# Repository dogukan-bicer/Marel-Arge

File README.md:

# Marel-Arge
marel arge çalışma dosyaları

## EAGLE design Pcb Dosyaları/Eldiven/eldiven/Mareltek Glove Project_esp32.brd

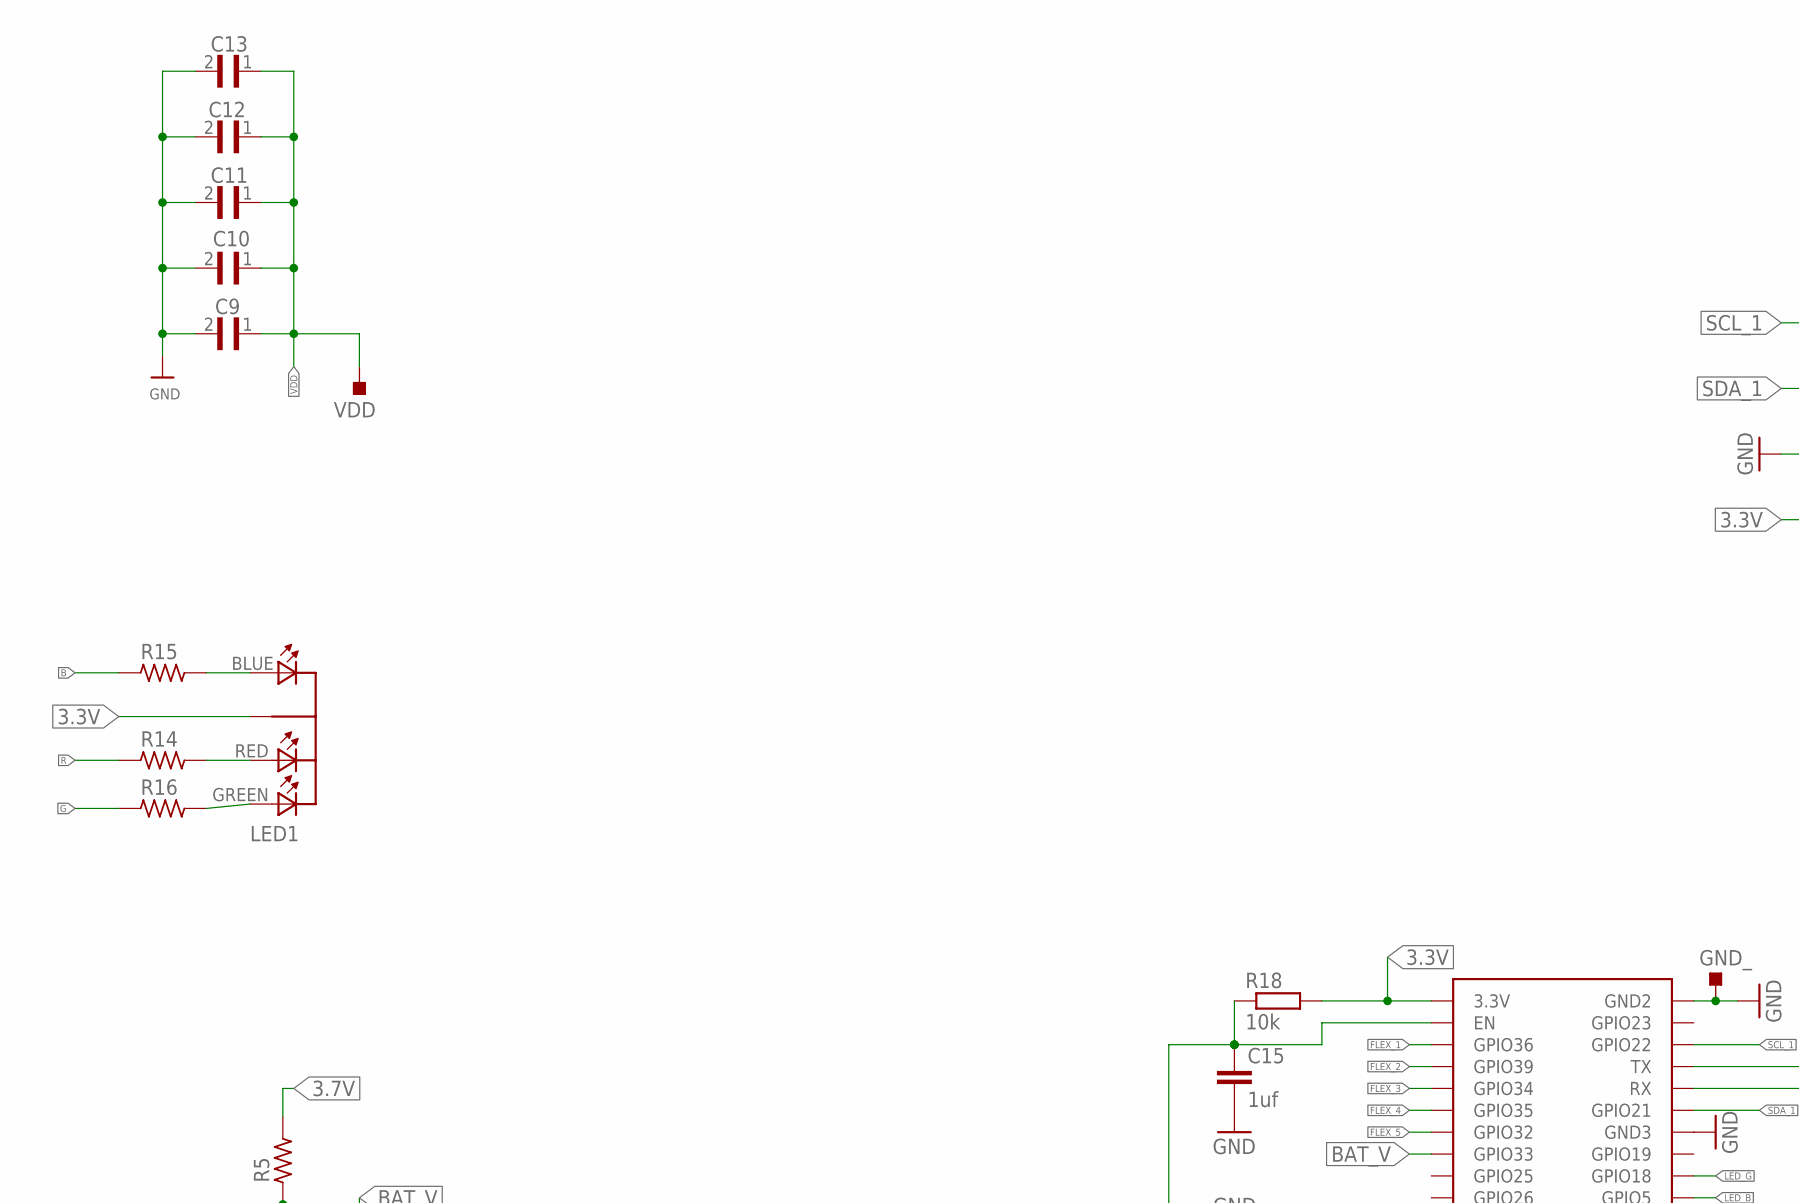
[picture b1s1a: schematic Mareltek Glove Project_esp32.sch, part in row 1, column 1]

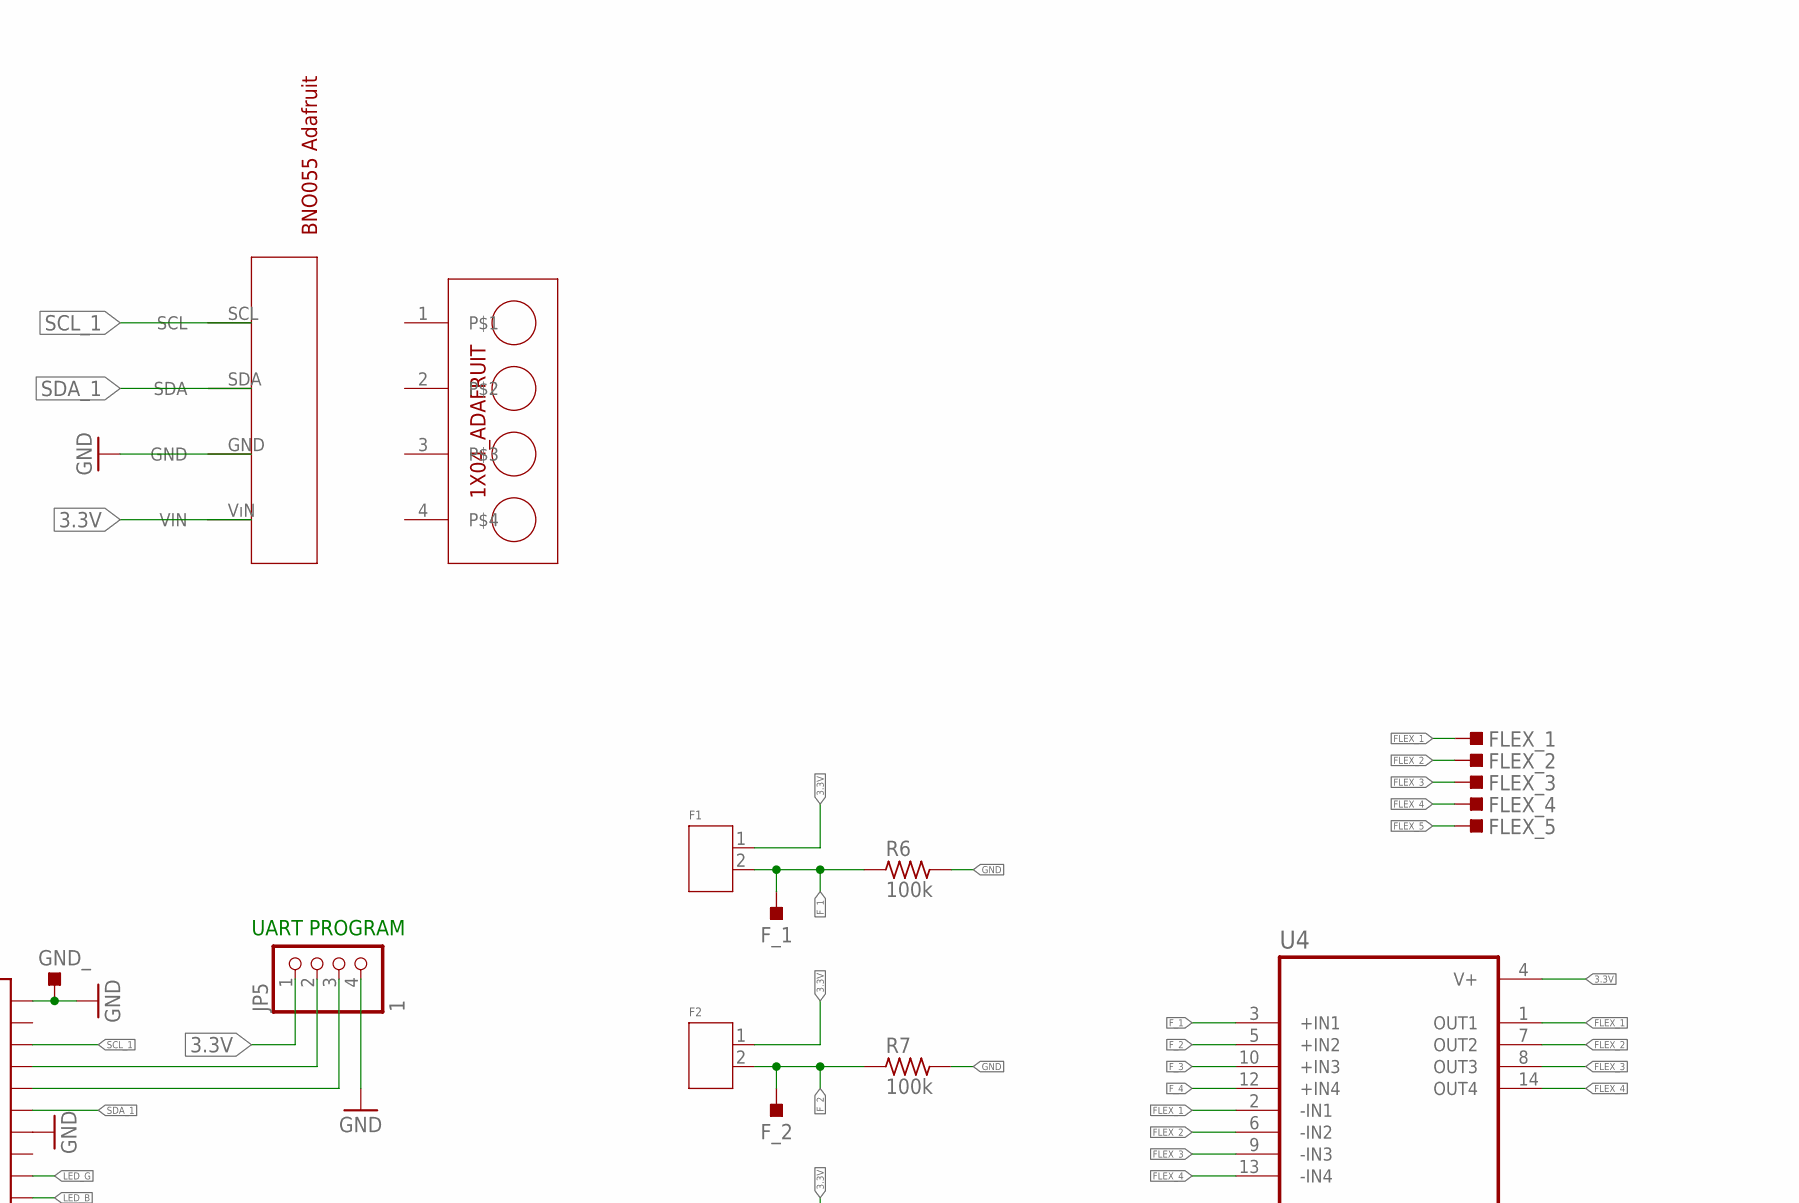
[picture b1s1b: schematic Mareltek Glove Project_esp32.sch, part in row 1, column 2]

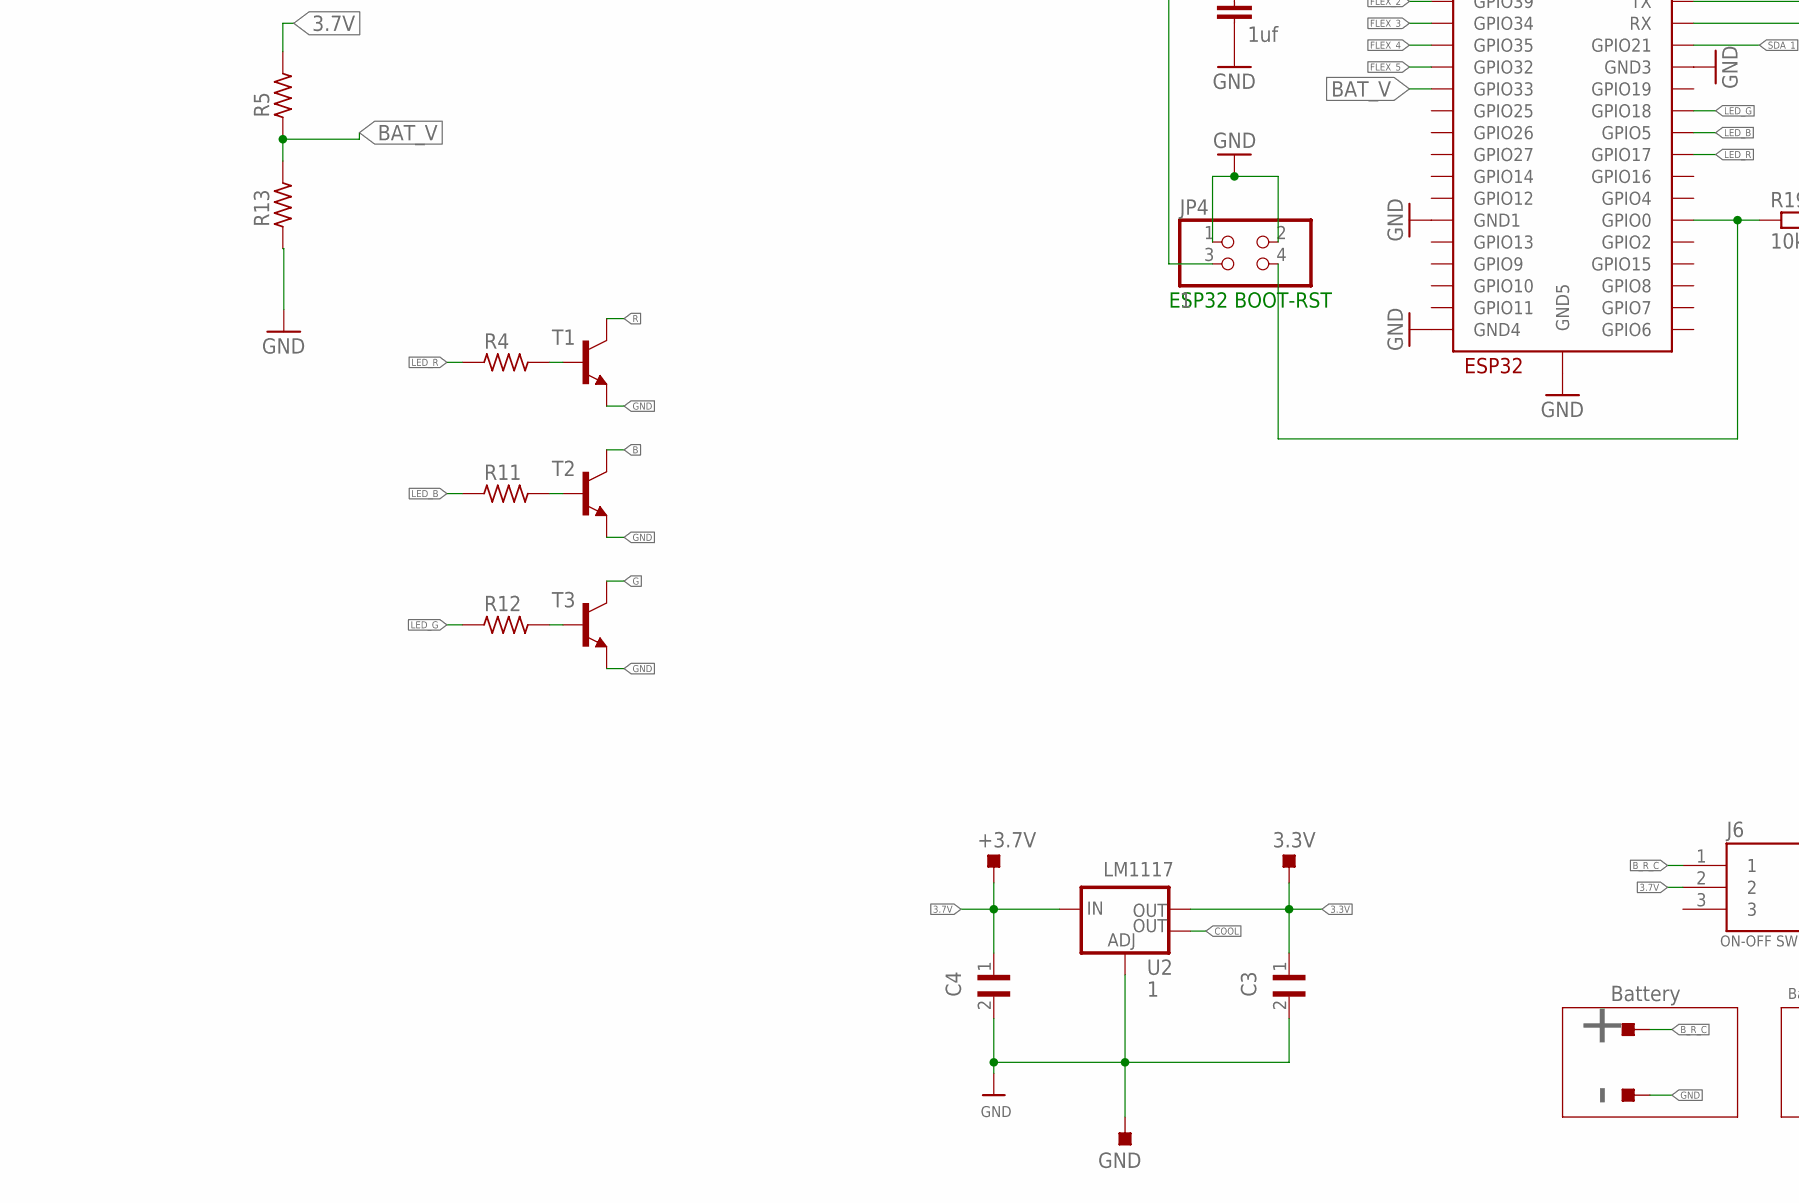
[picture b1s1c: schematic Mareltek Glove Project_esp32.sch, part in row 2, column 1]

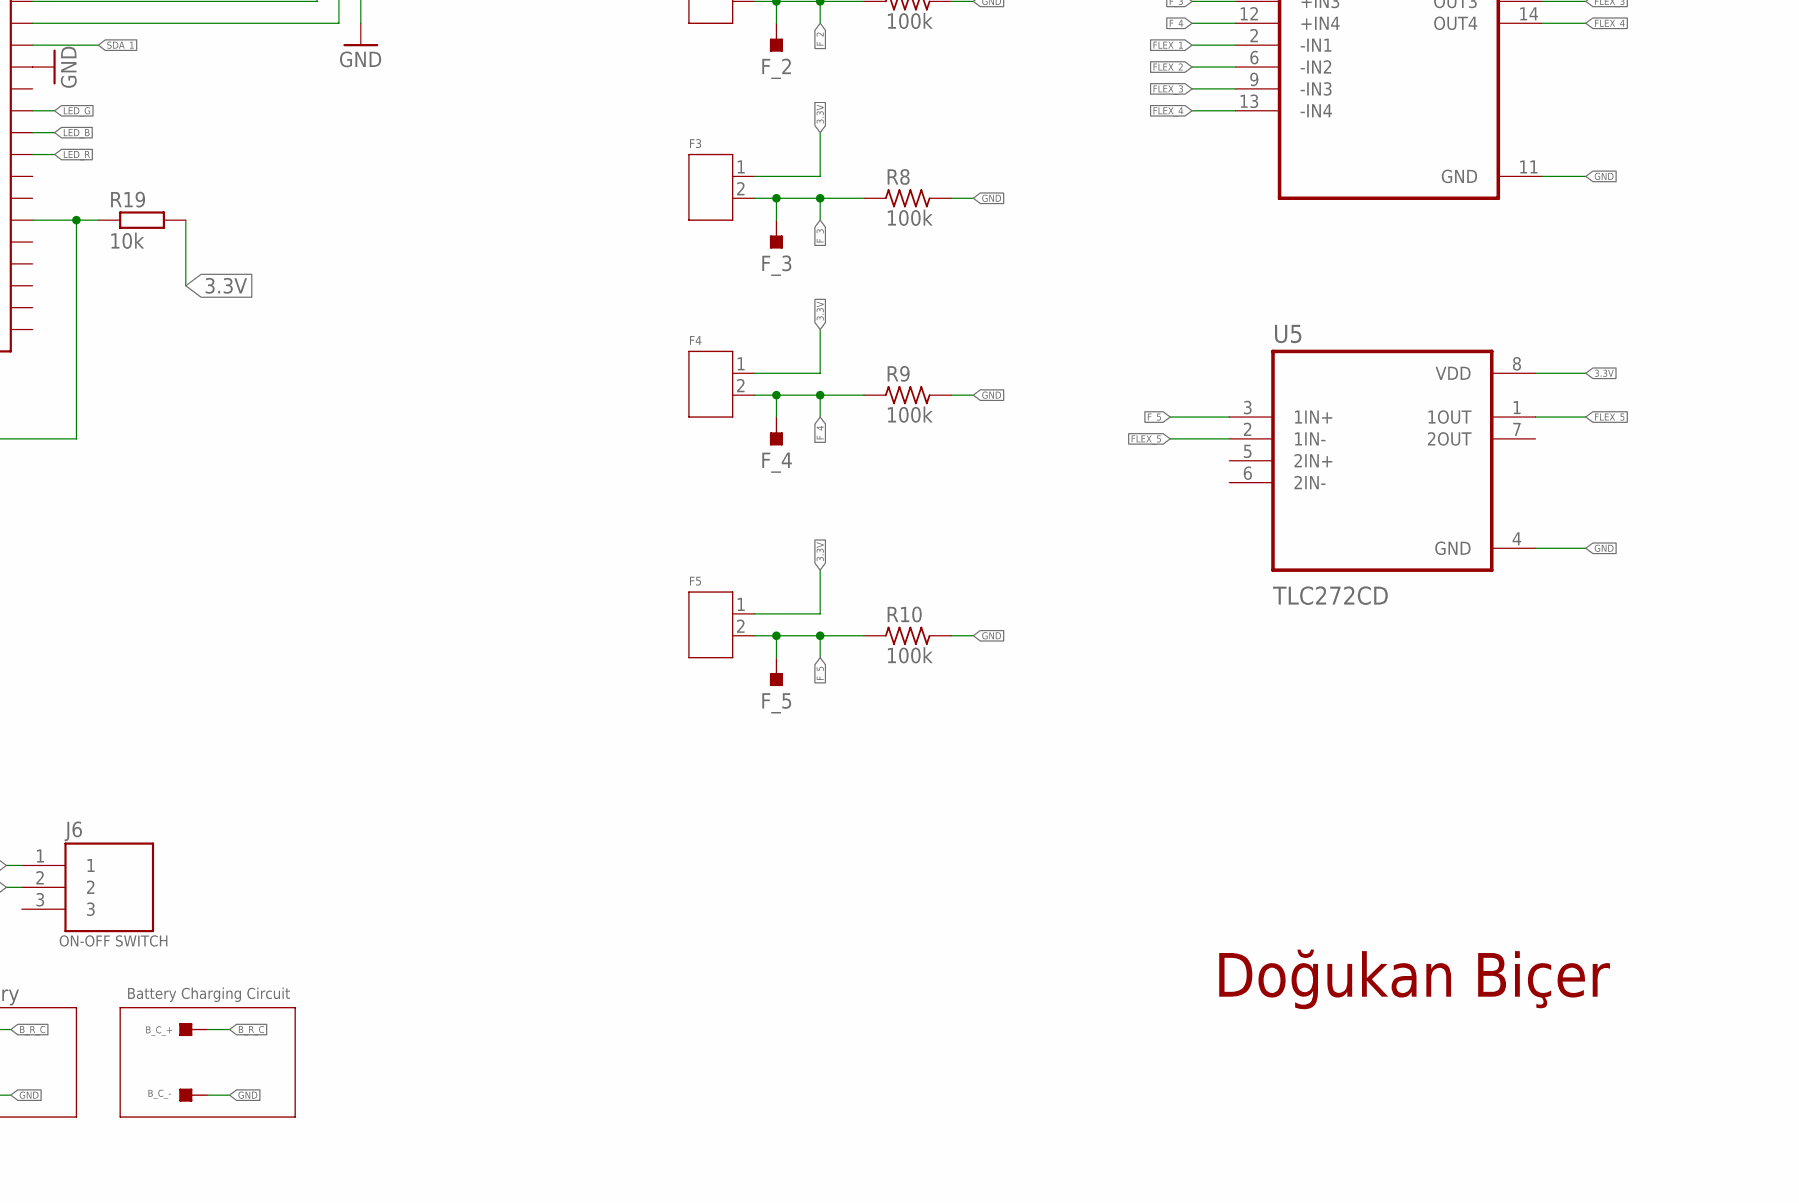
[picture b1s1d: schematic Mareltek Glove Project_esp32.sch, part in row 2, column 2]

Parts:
3.3V: TESTPOINT_TPS-SMD-10SN; TESTPOINT_SMD-10SN
+: TESTPOINT_TPS-PAD-036; TESTPOINT_PAD-036
+3.7V: TESTPOINT_TPS-SMD-10SN; TESTPOINT_SMD-10SN
-: TESTPOINT_TPS-PAD-036; TESTPOINT_PAD-036
B_C_+: TESTPOINT_TPS-PAD-036; TESTPOINT_PAD-036
B_C_-: TESTPOINT_TPS-PAD-036; TESTPOINT_PAD-036
C3, C4: 10uF; CAPC1608X90
C9, C10, C11, C12, C13: 100nF; CAPC1608X90
C15: 1uf; C0805
F1, F2, F3, F4, F5: FLEX_CONNECTOR
FLEX_1, FLEX_2, FLEX_3, FLEX_4, FLEX_5: TESTPOINT_TPS-SMD-10SN; TESTPOINT_SMD-10SN
F_1, F_2, F_3, F_4, F_5: TESTPOINT_TPS-SMD-10SN; TESTPOINT_SMD-10SN
GND: TESTPOINT_TPS-SMD-10SN; TESTPOINT_SMD-10SN
GND_: TESTPOINT_TPS-SMD-10SN; TESTPOINT_SMD-10SN
J6: ON-OFF SWITCH; TE_5-146293-3
JP4: 1; 2X02
JP5: 1; 1X04
LED1: LED-DIP-3; DIP-4
R4, R11, R12, R14, R15, R16: 100R; RC-MASTER-SMD_R0603MP
R5, R6, R7, R8, R9, R10: 100k; RC-MASTER-SMD_R0603MP
R13: 330R; RC-MASTER-SMD_R0603MP
R18, R19: 10k; R0603
T1, T2, T3: TRANSISTORBC846BLT1SOT23-BEC; SOT23-BEC
U2: 1; SOT223
U4: LM324; SOIC127P600X175-14N
U5: TLC272CD; SOIC127P599X175-8N
U$2: BNO055_ADAFRUIT; 1X06_ROUND_76
U$4: 1X04_ADAFRUIT; 1X04_ROUND_76
U$7: ESP32-WROOM
VDD: TESTPOINT_TPS-SMD-10SN; TESTPOINT_SMD-10SN

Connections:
3.3V: 3.3V.TP, C3.1, F1.1, F2.1, F3.1, F4.1, F5.1, JP5.1, LED1.COMMON_CATHODE (COM-CATHODE), R18.2, R19.2, U2.2 (OUT), U4.4 (V+), U5.8 (VDD), U$2.VıN (VIN), U$7.3V3 (3.3V)
3.7V: +3.7V.TP, C4.1, J6.2, R5.2, U2.3 (IN)
B: R15.1, T2.C
BAT_V: R5.1, R13.2, U$7.IO33 (GPIO33)
B_R_C: +.1, B_C_+.1, J6.1
COOL: U2.4 (OUT)
ESP32_RESET: C15.1, JP4.3, R18.1, U$7.EN
FLEX_1: FLEX_1.TP, U4.1 (OUT1), U4.2 (-IN1), U$7.SENSOR_VP (GPIO36)
FLEX_2: FLEX_2.TP, U4.6 (-IN2), U4.7 (OUT2), U$7.SENSOR_VN (GPIO39)
FLEX_3: FLEX_3.TP, U4.8 (OUT3), U4.9 (-IN3), U$7.IO34 (GPIO34)
FLEX_4: FLEX_4.TP, U4.13 (-IN4), U4.14 (OUT4), U$7.IO35 (GPIO35)
FLEX_5: FLEX_5.TP, U5.1 (1OUT), U5.2 (1IN-), U$7.IO32 (GPIO32)
F_1: F1.2, F_1.TP, R6.1, U4.3 (+IN1)
F_2: F2.2, F_2.TP, R7.1, U4.5 (+IN2)
F_3: F3.2, F_3.TP, R8.1, U4.10 (+IN3)
F_4: F4.2, F_4.TP, R9.1, U4.12 (+IN4)
F_5: F5.2, F_5.TP, R10.1, U5.3 (1IN+)
G: R16.1, T3.C
GND: -.1, B_C_-.1, C3.2, C4.2, C9.2, C10.2, C11.2, C12.2, C13.2, C15.2, GND.TP, GND_.TP, JP4.1, JP4.2, JP5.4, R6.2, R7.2, R8.2, R9.2, R10.2, R13.1, T1.E, T2.E, T3.E, U2.1 (ADJ), U4.11 (GND), U5.4 (GND), U$2.GND, U$7.GND1, U$7.GND2, U$7.GND3, U$7.GND4, U$7.GND5
LED_B: R11.1, U$7.IO5 (GPIO5)
LED_G: R12.1, U$7.IO18 (GPIO18)
LED_R: R4.1, U$7.IO17 (GPIO17)
unnamed: R4.2, T1.B
unnamed: R11.2, T2.B
unnamed: LED1.RED, R14.2
unnamed: LED1.BLUE, R15.2
unnamed: LED1.GREEN, R16.2
unnamed: R12.2, T3.B
unnamed: JP5.2, U$7.TX
unnamed: JP5.3, U$7.RX
unnamed: JP4.4, R19.1, U$7.IO0 (GPIO0)
R: R14.1, T1.C
SCL_1: U$2.SCL, U$7.IO22 (GPIO22)
SDA_1: U$2.SDA, U$7.IO21 (GPIO21)
VDD: C9.1, C10.1, C11.1, C12.1, C13.1, VDD.TP

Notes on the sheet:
Doğukan Biçer
LM1117
Battery
Battery Charging Circuit
ESP32 BOOT-RST
UART PROGRAM

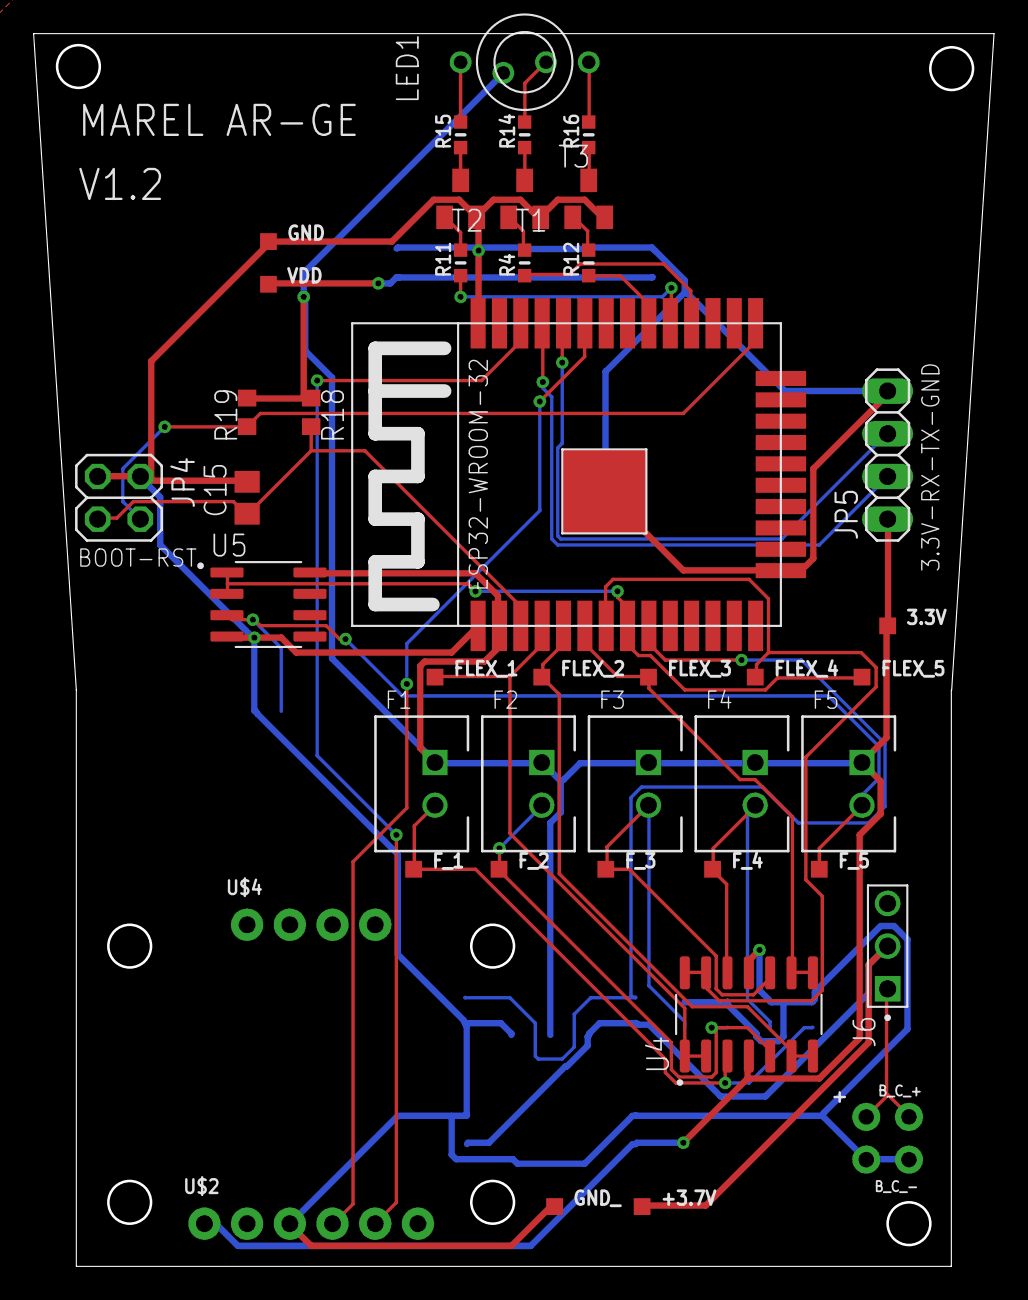
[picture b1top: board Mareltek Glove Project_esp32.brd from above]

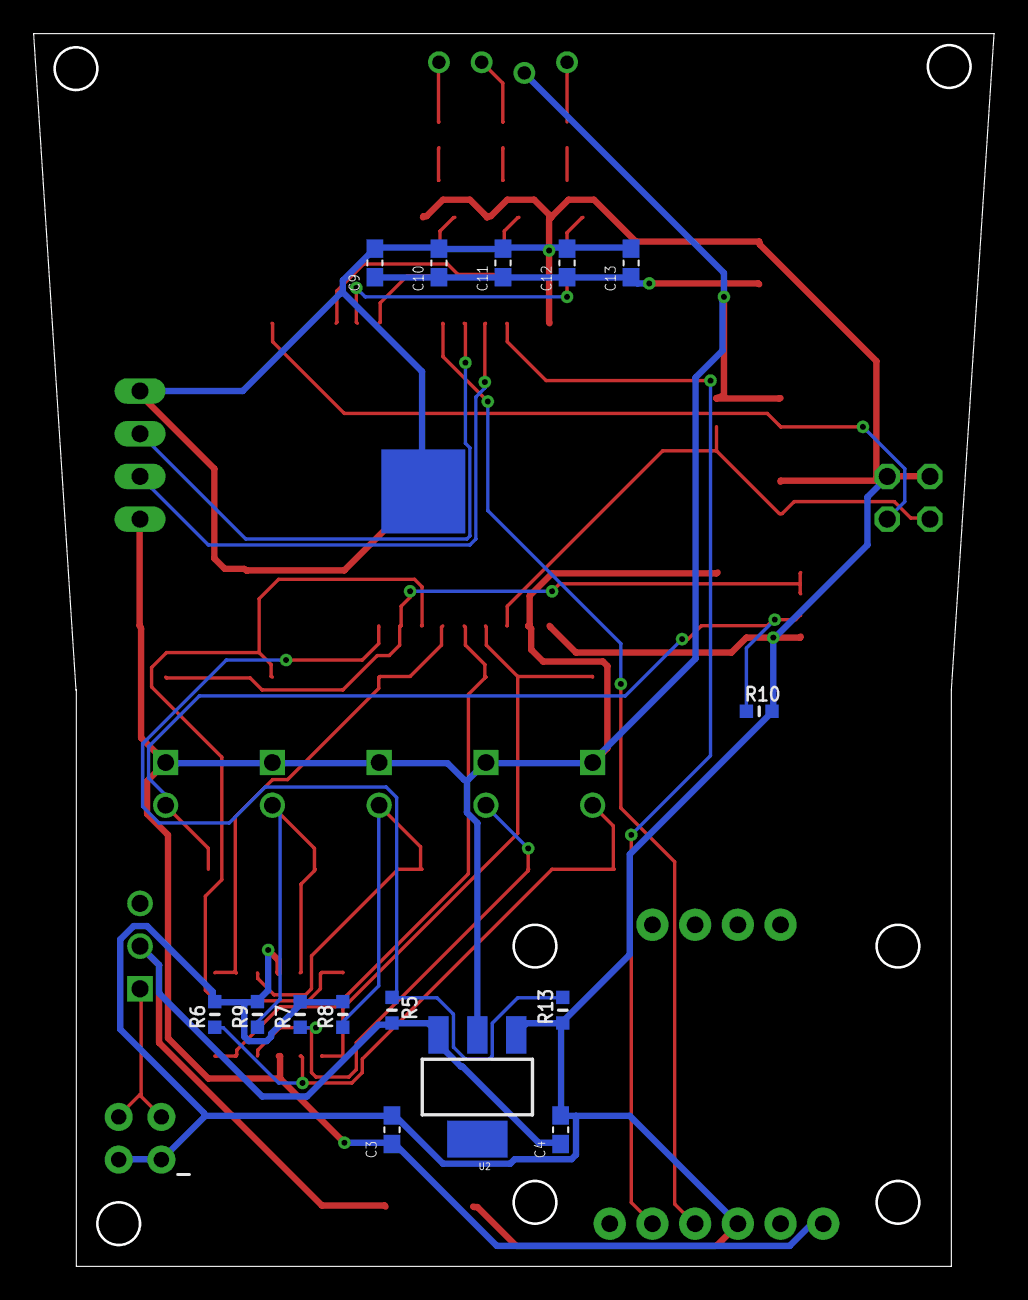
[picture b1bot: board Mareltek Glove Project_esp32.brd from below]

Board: 2 copper layers, 57.0 x 73.2 mm, 60 parts (16 on the bottom side), 34 nets.

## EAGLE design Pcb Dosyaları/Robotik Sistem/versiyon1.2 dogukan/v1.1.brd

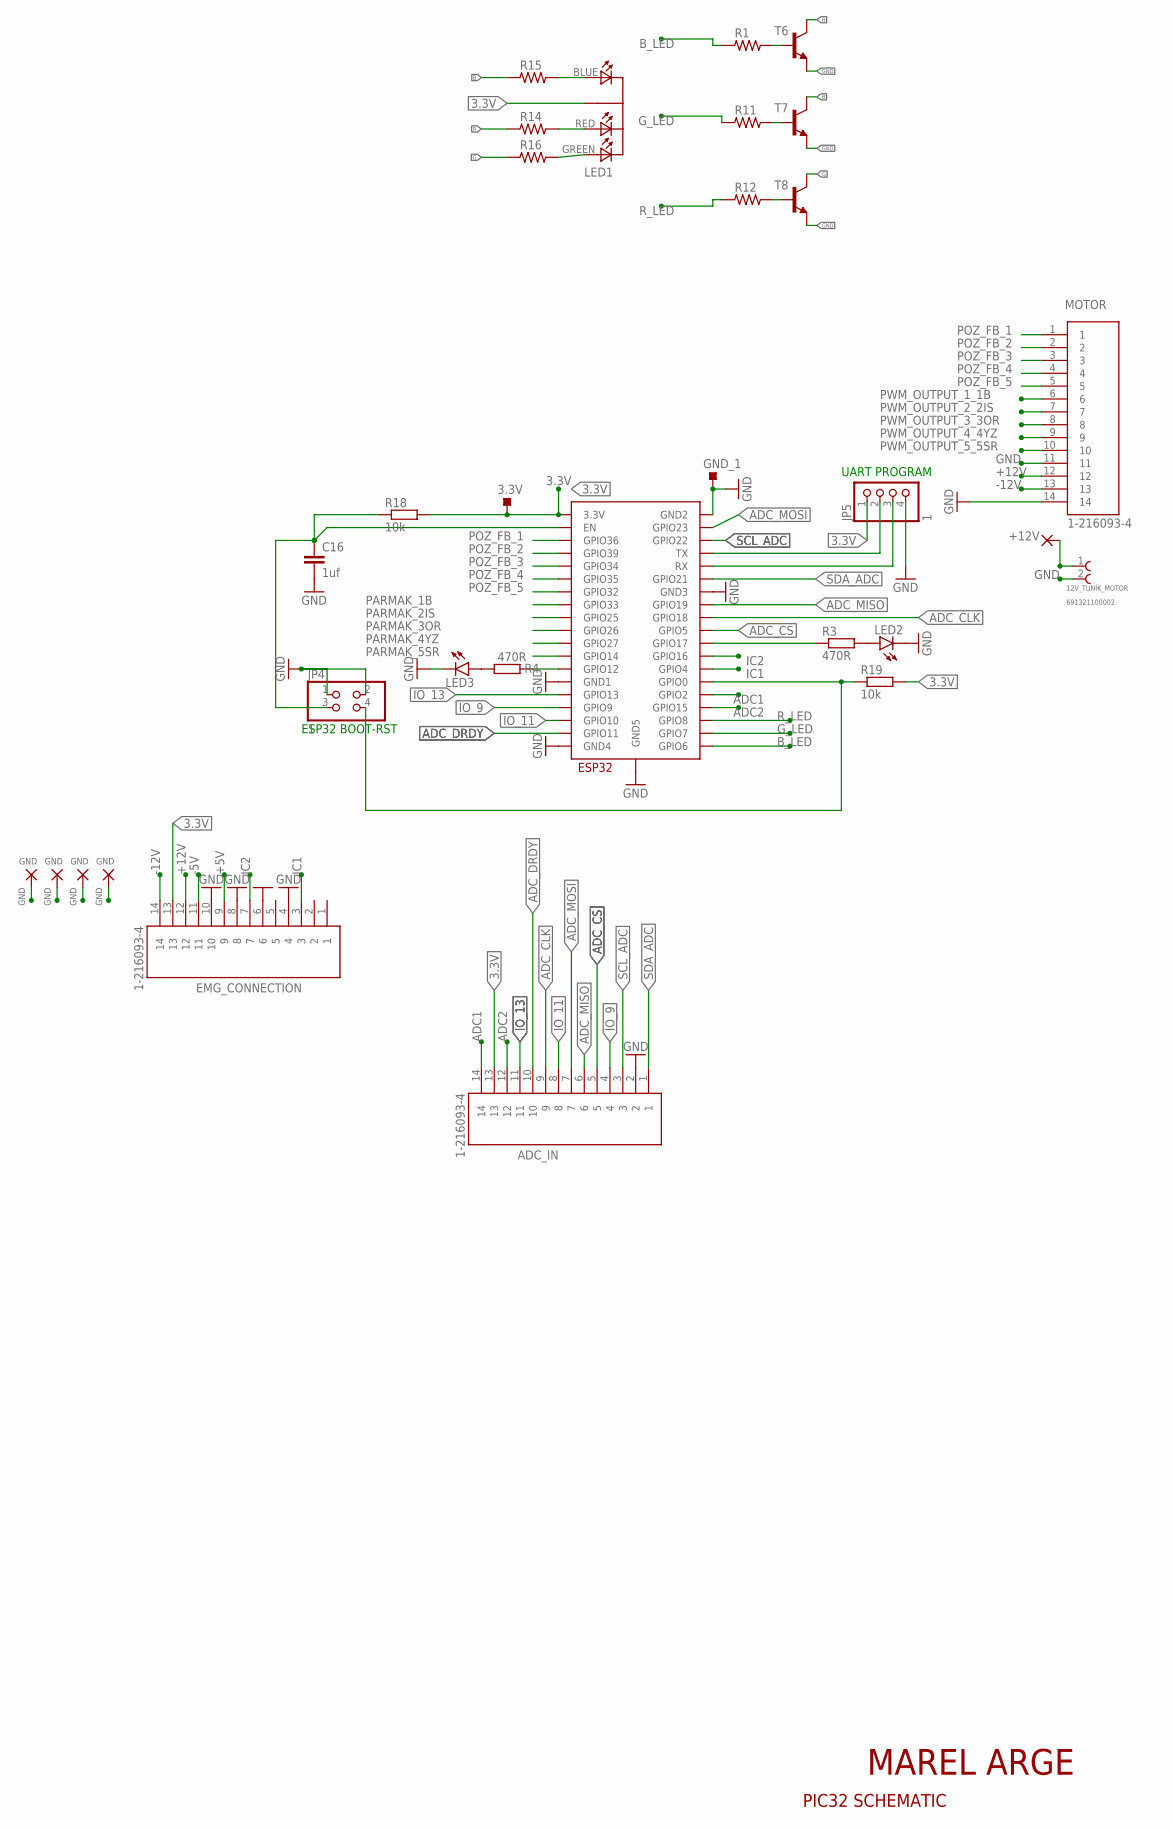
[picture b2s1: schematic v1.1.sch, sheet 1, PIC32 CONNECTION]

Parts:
3.3V: TESTPOINT_TPS-SMD-10SN; TESTPOINT_SMD-10SN
12VOLT: 12V; 2,54/0,8
12V_TUNİK_MOTOR: 691321100002
ADC_IN: 1-216093-4; TE_1-216093-4
C16: 1uf; C0805
EMG_CONNECTION: 1-216093-4; TE_1-216093-4
GND18, GND19, GND20, GND21: GND; 2,54/0,8
GND_1: TESTPOINT_TPS-SMD-10SN; TESTPOINT_SMD-10SN
JP4: 1; 2X02
JP5: 1; 1X04
LED1: LED-DIP-3; DIP-4
LED2, LED3: LED5MM
MOTOR: 1-216093-4; TE_1-216093-4
R1, R11, R12, R14, R15, R16: 100R; RC-MASTER-SMD_R0603MP
R3, R4: 470R; R0603
R18, R19: 10k; R0603
T6, T7, T8: TRANSISTORBC846BLT1SOT23-BEC; SOT23-BEC
U$7: ESP32-WROOM

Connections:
3.3V: 3.3V.TP, ADC_IN.13, EMG_CONNECTION.13, JP5.1, LED1.COMMON_CATHODE (COM-CATHODE), R18.2, R19.2, U$7.3V3 (3.3V); also elsewhere on the board
+5V: EMG_CONNECTION.9; also elsewhere on the board
+12V: 12VOLT.1, 12V_TUNİK_MOTOR.1, EMG_CONNECTION.12, MOTOR.12; also elsewhere on the board
-5V: EMG_CONNECTION.11; also elsewhere on the board
-12V: EMG_CONNECTION.14, MOTOR.13; also elsewhere on the board
ADC1: ADC_IN.14, U$7.IO2 (GPIO2)
ADC2: ADC_IN.12, U$7.IO15 (GPIO15)
ADC_CLK: ADC_IN.9, U$7.IO18 (GPIO18)
ADC_CS: ADC_IN.5, U$7.IO5 (GPIO5)
ADC_DRDY: ADC_IN.10, U$7.CMD (GPIO11)
ADC_MISO: ADC_IN.6, U$7.IO19 (GPIO19)
ADC_MOSI: ADC_IN.7, U$7.IO23 (GPIO23)
B: R14.1, T7.C
B_LED: R1.1, U$7.CLK (GPIO6)
ESP32_RESET: C16.1, JP4.3, R18.1, U$7.EN
G: R16.1, T8.C
GND: 12V_TUNİK_MOTOR.2, ADC_IN.2, C16.2, EMG_CONNECTION.4, EMG_CONNECTION.6, EMG_CONNECTION.8, EMG_CONNECTION.10, GND18.1, GND19.1, GND20.1, GND21.1, GND_1.TP, JP4.1, JP4.2, JP5.4, LED2.K (C), LED3.K (C), MOTOR.11, MOTOR.14, T6.E, T7.E, T8.E, U$7.GND1, U$7.GND2, U$7.GND3, U$7.GND4, U$7.GND5; also elsewhere on the board
G_LED: R11.1, U$7.SD0 (GPIO7)
IC1: EMG_CONNECTION.3, U$7.IO4 (GPIO4)
IC2: EMG_CONNECTION.7, U$7.IO16 (GPIO16)
IO_9: ADC_IN.4, U$7.SD2 (GPIO9)
IO_11: ADC_IN.8, U$7.SD3 (GPIO10)
IO_13: ADC_IN.11, U$7.IO13 (GPIO13)
unnamed: R11.2, T7.B
unnamed: R1.2, T6.B
unnamed: LED1.RED, R14.2
unnamed: R12.2, T8.B
unnamed: LED1.BLUE, R15.2
unnamed: LED1.GREEN, R16.2
unnamed: JP5.2, U$7.TX
unnamed: JP5.3, U$7.RX
unnamed: JP4.4, R19.1, U$7.IO0 (GPIO0)
unnamed: LED2.A, R3.2
unnamed: R3.1, U$7.IO17 (GPIO17)
unnamed: LED3.A, R4.2
unnamed: R4.1, U$7.IO12 (GPIO12)
PARMAK_1B: U$7.IO33 (GPIO33); also elsewhere on the board
PARMAK_2IS: U$7.IO25 (GPIO25); also elsewhere on the board
PARMAK_3OR: U$7.IO26 (GPIO26); also elsewhere on the board
PARMAK_4YZ: U$7.IO27 (GPIO27); also elsewhere on the board
PARMAK_5SR: U$7.IO14 (GPIO14); also elsewhere on the board
POZ_FB_1: MOTOR.1, U$7.SENSOR_VP (GPIO36)
POZ_FB_2: MOTOR.2, U$7.SENSOR_VN (GPIO39)
POZ_FB_3: MOTOR.3, U$7.IO34 (GPIO34)
POZ_FB_4: MOTOR.4, U$7.IO35 (GPIO35)
POZ_FB_5: MOTOR.5, U$7.IO32 (GPIO32)
PWM_OUTPUT_1_1B: MOTOR.6; also elsewhere on the board
PWM_OUTPUT_2_2IS: MOTOR.7; also elsewhere on the board
PWM_OUTPUT_3_3OR: MOTOR.8; also elsewhere on the board
PWM_OUTPUT_4_4YZ: MOTOR.9; also elsewhere on the board
PWM_OUTPUT_5_5SR: MOTOR.10; also elsewhere on the board
R: R15.1, T6.C
R_LED: R12.1, U$7.SD1 (GPIO8)
SCL_ADC: ADC_IN.3, U$7.IO22 (GPIO22)
SDA_ADC: ADC_IN.1, U$7.IO21 (GPIO21)

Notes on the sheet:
MAREL ARGE
PIC32 SCHEMATIC
ESP32 BOOT-RST
UART PROGRAM
-12V
+12V

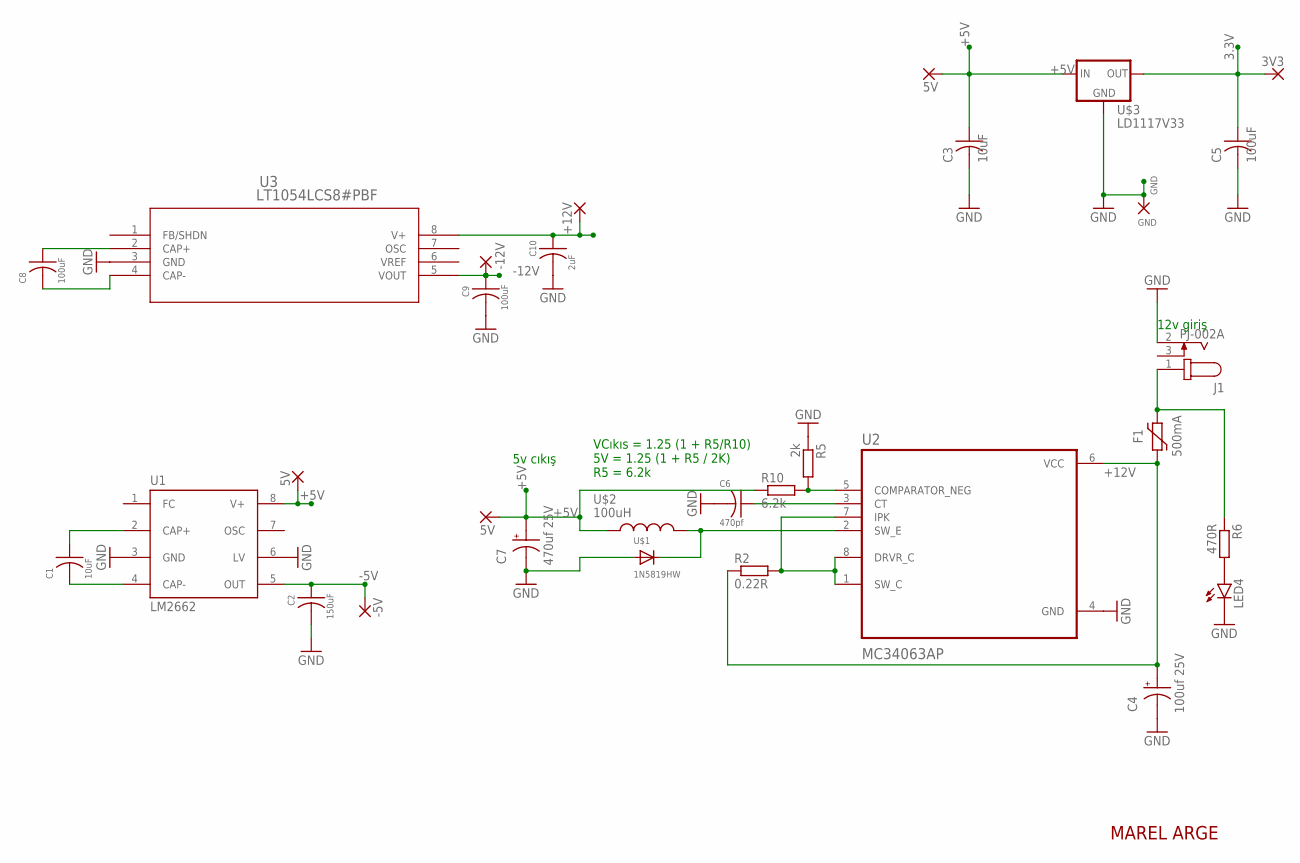
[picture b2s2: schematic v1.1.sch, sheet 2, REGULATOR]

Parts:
3V3_1: 3V3; 2,54/0,8
5V, 5V1: 5V; 2,54/0,8
+5V: 5V; 2,54/0,8
+12V: +12V; 2,54/0,8
-5V: -5V; 2,54/0,8
-12V: -12V; 2,54/0,8
C1, C3: 10uF; C1206
C2: 150uF; C1206
C4: 100uf 25V; X
C5, C8, C9: 100uF; C1206
C6: 470pf; C1206
C7: 470uf 25V; X
C10: 2uF; C1206
F1: 500mA; 1206L
GND13: GND; 2,54/0,8
J1: PJ-002A; CUI_PJ-002A
LED4: LED5MM
R2: 0.22R; R2512
R5: 2k; R0805
R6: 470R; R0603
R10: 6.2k; R0805
U1: LM2662; SO08
U2: MC34063AP; DIP794W45P254L959H508Q8
U3: LT1054LCS8#PBF; SO-8_S
U$1: 1N5819HW; SOD-123-EDITED
U$2: 100uH; L7070
U$3: LD1117V33

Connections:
3.3V: 3V3_1.1, C5.1, U$3.OUT; also elsewhere on the board
12_IN: F1.P$2 (2), J1.1, R6.1
+5V: 5V.1, 5V1.1, +5V.1, C3.1, C7.A, R10.1, U1.8 (V+), U$2.1, U$3.IN; also elsewhere on the board
+12V: +12V.1, C4.A, C10.1, F1.P$1 (1), R2.1, U2.6 (VCC), U3.8 (V+); also elsewhere on the board
-5V: -5V.1, C2.1, U1.5 (OUT); also elsewhere on the board
-12V: -12V.1, C9.1, U3.5 (VOUT); also elsewhere on the board
GND: C2.2, C3.2, C4.C, C5.2, C6.2, C7.C, C9.2, C10.2, GND13.1, J1.2, LED4.K (C), R5.1, U1.3 (GND), U1.6 (LV), U2.4 (GND), U3.3 (GND), U$1.A, U$3.GND; also elsewhere on the board
unnamed: C1.1, U1.2 (CAP+)
unnamed: C1.2, U1.4 (CAP-)
unnamed: R2.2, U2.1 (SW_C), U2.7 (IPK), U2.8 (DRVR_C)
unnamed: C8.1, U3.2 (CAP+)
unnamed: U2.2 (SW_E), U$1.C, U$2.2
unnamed: R5.2, R10.2, U2.5 (COMPARATOR_NEG)
unnamed: C6.1, U2.3 (CT)
unnamed: C8.2, U3.4 (CAP-)
unnamed: LED4.A, R6.2
VREF: U3.6 (VREF)

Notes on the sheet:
MAREL ARGE
5v cıkış
12v giriş
VCıkıs = 1.25 (1 + R5/R10) 5V = 1.25 (1 + R5 / 2K) R5 = 6.2k

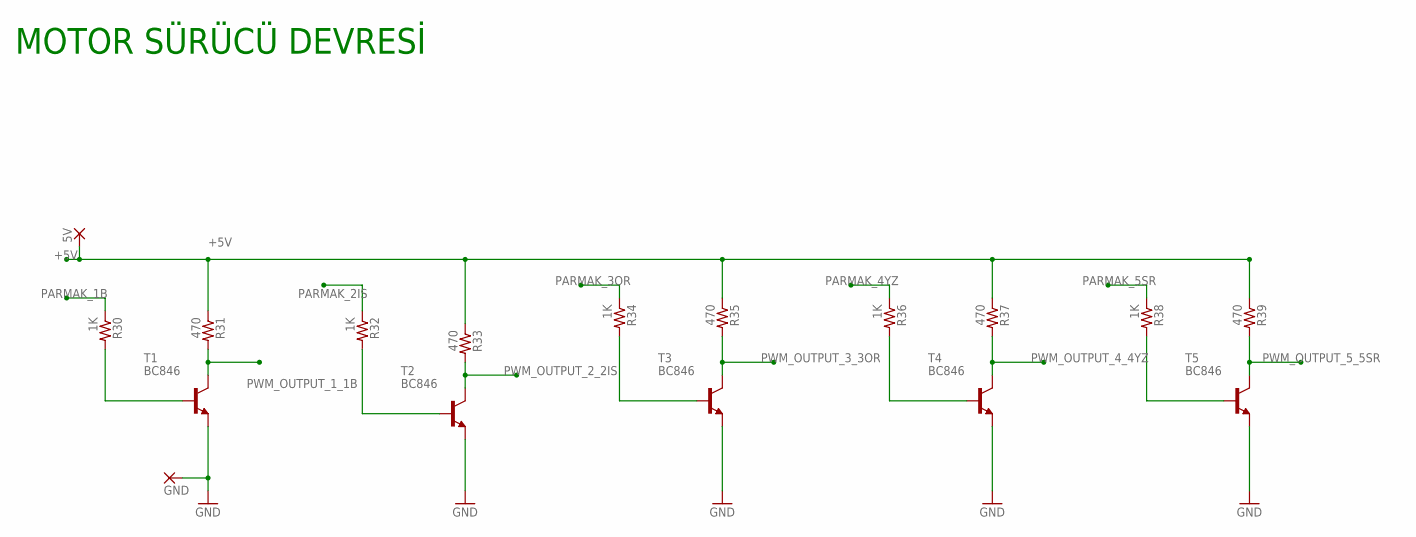
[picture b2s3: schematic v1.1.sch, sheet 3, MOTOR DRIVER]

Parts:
GND_: GND; 2,54/0,8
R30, R32, R34, R36, R38: 1K; M0805
R31, R33, R35, R37, R39: 470; M0805
T1, T2, T3, T4, T5: BC846; SOT23
_5VOLT: 5V; 2,54/0,8

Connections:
+5V: R31.1, R33.1, R35.1, R37.1, R39.1, _5VOLT.1; also elsewhere on the board
GND: GND_.1, T1.2 (E), T2.2 (E), T3.2 (E), T4.2 (E), T5.2 (E); also elsewhere on the board
unnamed: R30.2, T1.1 (B)
unnamed: R32.2, T2.1 (B)
unnamed: R34.2, T3.1 (B)
unnamed: R36.2, T4.1 (B)
unnamed: R38.2, T5.1 (B)
PARMAK_1B: R30.1; also elsewhere on the board
PARMAK_2IS: R32.1; also elsewhere on the board
PARMAK_3OR: R34.1; also elsewhere on the board
PARMAK_4YZ: R36.1; also elsewhere on the board
PARMAK_5SR: R38.1; also elsewhere on the board
PWM_OUTPUT_1_1B: R31.2, T1.3 (C); also elsewhere on the board
PWM_OUTPUT_2_2IS: R33.2, T2.3 (C); also elsewhere on the board
PWM_OUTPUT_3_3OR: R35.2, T3.3 (C); also elsewhere on the board
PWM_OUTPUT_4_4YZ: R37.2, T4.3 (C); also elsewhere on the board
PWM_OUTPUT_5_5SR: R39.2, T5.3 (C); also elsewhere on the board

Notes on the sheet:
MOTOR SÜRÜCÜ DEVRESİ

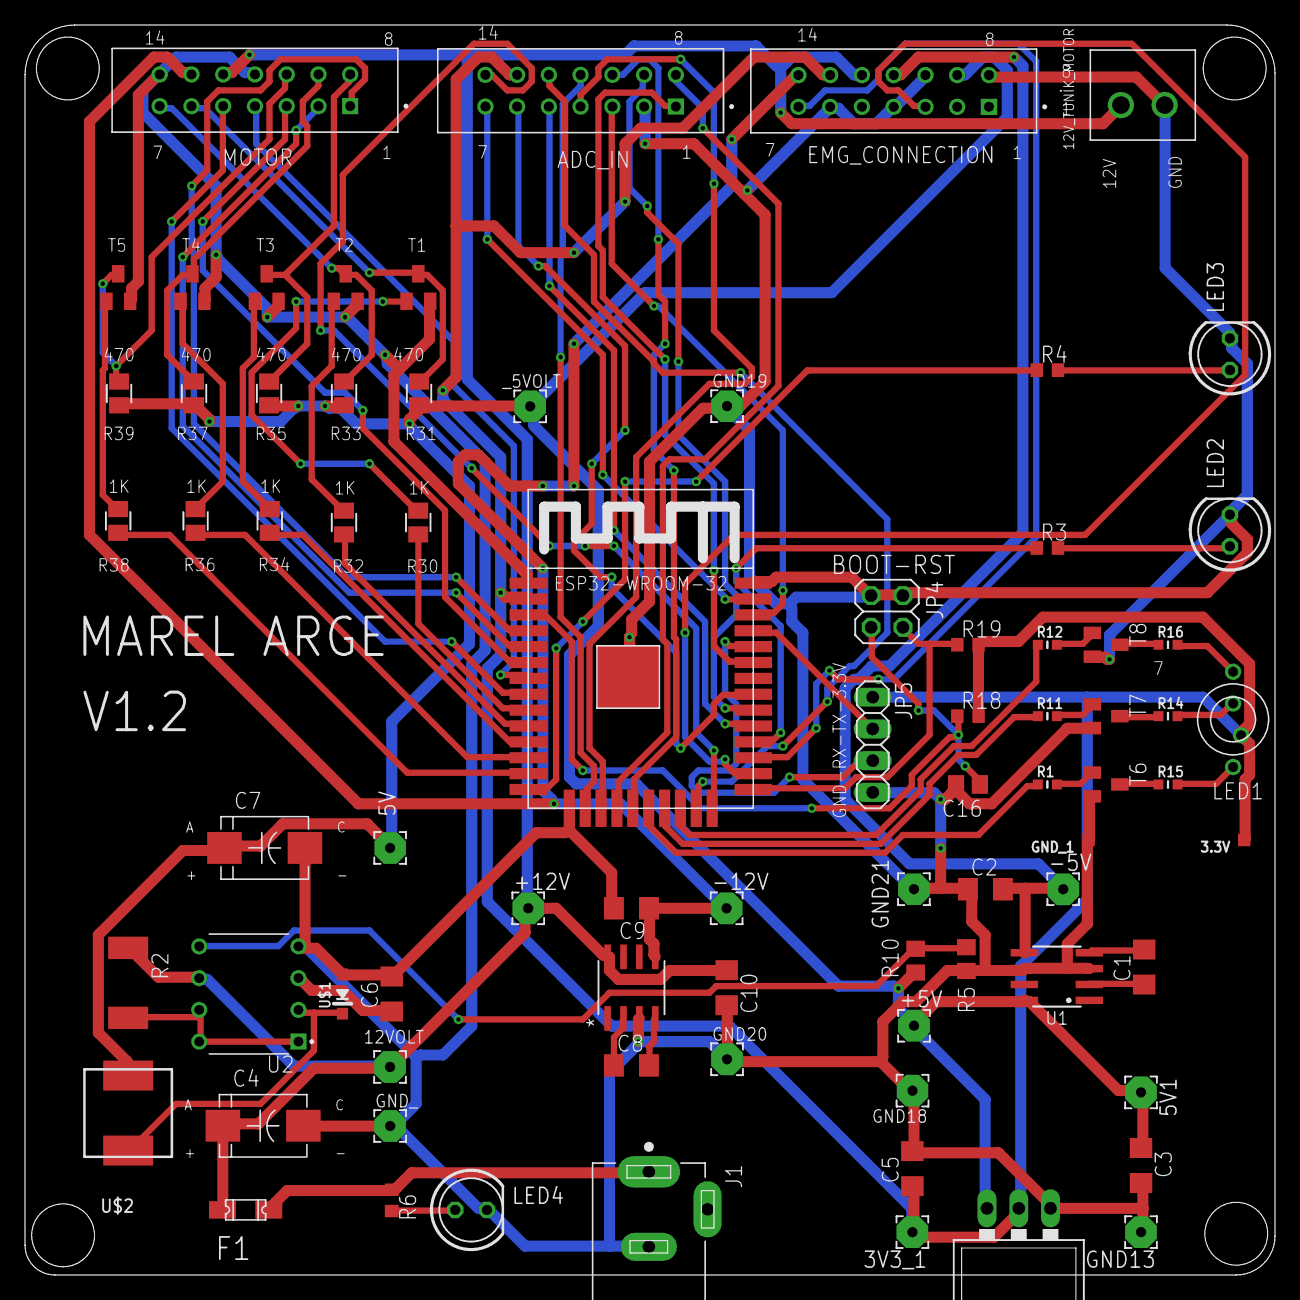
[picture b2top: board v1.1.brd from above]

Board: 2 copper layers, 100.0 x 100.0 mm, 79 parts (0 on the bottom side), 70 nets.

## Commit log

2024-05-18 Create Pcb Dosyalari
2024-07-24 Rename eldiven_udp.cpp to udp_robotik.cpp
2024-07-24 Rename udp_robotik.cpp to udp_eldiven.cpp
2024-07-24 Rename robotik_el_esp32.cpp to udp_robotik.cpp
2024-07-26 Rename udp_ve_bluetooth.cpp to robotik_udp_ve_bluetooth.cpp
2024-07-26 Rename robotik_udp_ve_bluetooth.cpp to udp_ve_bluetooth_robotik.cpp
2024-11-04 Create Python

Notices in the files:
parts and their libraries:
Volks73-Kemet: Creative Commons Attribution-ShareAlike 3.0 Unported (CC BY-SA 3.0), http://creativecommons.org/licenses/by-sa/3.0/.
SparkFun-Aesthetics: Licensing: Creative Commons ShareAlike 4.0 International - https://creativecommons.org/licenses/by-sa/4.0
